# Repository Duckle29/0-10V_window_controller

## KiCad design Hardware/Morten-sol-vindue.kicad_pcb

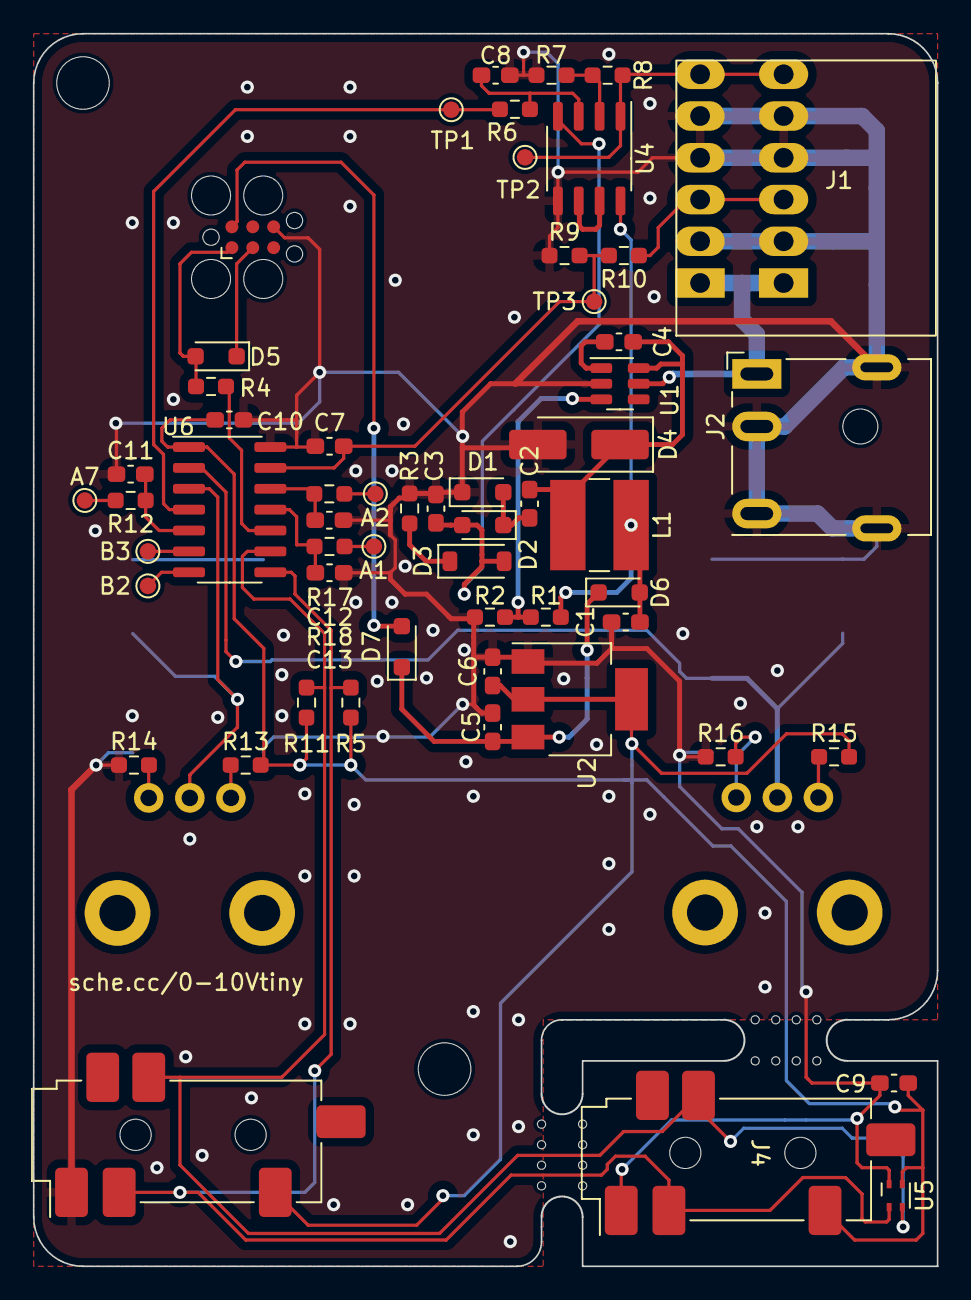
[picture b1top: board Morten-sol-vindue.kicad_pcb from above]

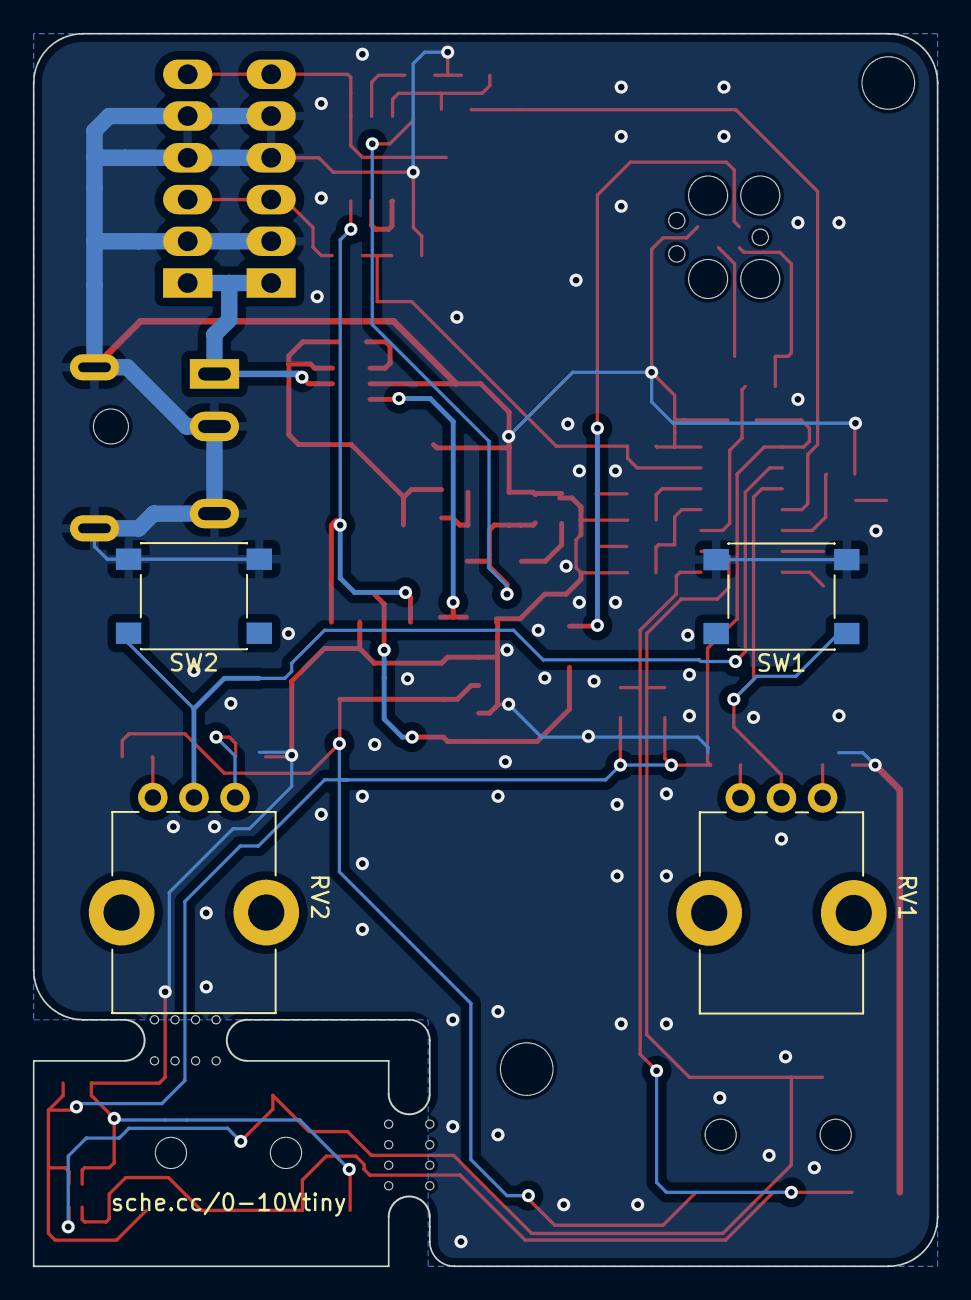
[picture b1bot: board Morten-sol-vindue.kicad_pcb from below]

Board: 2 copper layers, 55.0 x 75.0 mm, 61 parts (4 on the bottom side), 38 nets.

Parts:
A1, A2, A7: PA7; TestPoint_Pad_D1.0mm
B2, B3: PA7; TestPoint_Pad_D1.0mm
C1, C2, C3, C5, C6: 1uF 25V; C_0603_1608Metric_Pad1.08x0.95mm_HandSolder
C4, C7, C8, C9, C10, C11, C12, C13: 100nF; C_0603_1608Metric_Pad1.08x0.95mm_HandSolder
D1, D2, D5, D6, D7: BAT54WS; D_SOD-323_HandSoldering
D3: 15V; D_SOD-123
D4: SS12; D_SMA_Handsoldering
J1: CUI TBL009-254-06xx; TerminalBlock_Phoenix_PTSM-0,5-6-2.5-H-THR_1x06_P2.50mm_Hor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
J2: CUI_PJ-079BH; BarrelJack_CUI_PJ-079BH_Horizontal
J3: SJ-43514-SMT; Jack_3.5mm_CUI_SJ-43516-SMT_Horizontal
J4: AudioJack4; Jack_3.5mm_CUI_SJ-43516-SMT_Horizontal
J5: AVR-UPDI-6; Tag-Connect_TC2030-IDC-FP_2x03_P1.27mm_Vertical
L1: 1mH; L_TracoPower_TCK-047_5.2x5.8mm
R1: 150k; R_0603_1608Metric_Pad0.98x0.95mm_HandSolder
R2: 10k; R_0603_1608Metric_Pad0.98x0.95mm_HandSolder
R3, R12, R17, R18: 100R; R_0603_1608Metric_Pad0.98x0.95mm_HandSolder
R4: 470R; R_0603_1608Metric_Pad0.98x0.95mm_HandSolder
R5, R10, R11: 12k; R_0603_1608Metric_Pad0.98x0.95mm_HandSolder
R6, R14, R16: 1k; R_0603_1608Metric_Pad0.98x0.95mm_HandSolder
R7, R13, R15: 33k; R_0603_1608Metric_Pad0.98x0.95mm_HandSolder
R8: 100k; R_0603_1608Metric_Pad0.98x0.95mm_HandSolder
R9: 3k9; R_0603_1608Metric_Pad0.98x0.95mm_HandSolder
RV1, RV2: 100K; Potentiometer_Bourns_PTV09A-1_Single_Vertical
SW1, SW2: SW_Push; SW_Push_1P1T_NO_6x6mm_H9.5mm
TP1: DAC; TestPoint_Pad_D1.0mm
TP2: DACx4; TestPoint_Pad_D1.0mm
TP3: A3(0-10/~4); TestPoint_Pad_D1.0mm
U1: LV2862YDDCR; SOT-23-6
U2: AMS1117-3.3; SOT-223-3_TabPin2
U4: LM358; SO-8_3.9x4.9mm_P1.27mm
U5: SHT4x; Sensirion_DFN-4_1.5x1.5mm_P0.8mm_SHT4x_NoCentralPad
U6: ATtiny414-SS; SOIC-14_3.9x8.7mm_P1.27mm

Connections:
+3V3: C6.2, C9.2, C10.2, J3.T, J4.T, R5.1, R11.1, R13.2, R15.2, U2.2 (VO), U5.3 (VDD), U6.1 (VCC)
+12VA: C1.1, D6.2 (A), L1.2, R1.1, U4.8 (V+)
+24V: J1.1, J2.1, U1.5 (VIN)
-12VA: C3.2, D2.2 (A), D3.2 (A), U4.4 (V-)
/0-10V in: J1.3, R10.1
/0-10V out: J1.6, R8.2, TP2.1, U4.1
/Adapter RX: D5.2 (A), J5.1 (DATA), R4.2
/UPDI: R4.1, U6.10 (~RESET/PA0)
GND: C1.2, C3.1, C5.1, C6.1, C7.1, C8.1, C9.1, C10.1, C11.1, C12.1, C13.1, D1.1 (K), D4.2 (A), J1.2, J1.4, J1.5, J2.2, J2.3, J2.MP (MountPin), J3.S, J4.S, J5.6 (GND), R2.2, R3.2, R7.2, R9.1, R14.1, R16.1, SW1.2, SW2.2, U1.2 (GND), U2.1 (GND), U4.5 (+), U5.4 (VSS), U6.14 (GND)
unnamed: A1.1, R18.2
unnamed: A2.1, R17.2
unnamed: A7.1, R12.2
unnamed: C2.2, D1.2 (A), D2.1 (K)
unnamed: D3.1 (K), R3.1
unnamed: C2.1, C4.2, D4.1 (K), L1.1, U1.6 (SW)
unnamed: D5.1 (K), J5.3 (TX)
unnamed: C5.2, D6.1 (K), D7.1 (K), U2.3 (VI)
unnamed: R13.1, RV1.1
unnamed: R14.2, RV1.3
unnamed: R15.1, RV2.1
unnamed: R16.2, RV2.3
unnamed: C4.1, U1.1 (CB)
unnamed: R1.2, R2.1, U1.3 (FB)
unnamed: C8.2, R6.2, U4.3 (+)
unnamed: R7.1, R8.1, U4.2 (-)
unnamed: U4.6 (-), U4.7
unnamed: C13.2, R18.1, U6.11 (PA1)
unnamed: C12.2, R17.1, U6.12 (PA2)
unnamed: C7.2, R9.2, R10.2, TP3.1, U6.13 (PA3)
unnamed: R6.1, TP1.1, U6.4 (PA6)
unnamed: C11.2, R12.1, U6.5 (PA7)
unnamed: B2.1, U6.7 (PB2)
unnamed: B3.1, U6.6 (PB3)
SCL: J3.R1, J4.R1, R11.2, U5.2 (SCL), U6.9 (PB0)
SDA: J3.R2, J4.R2, R5.2, U5.1 (SDA), U6.8 (PB1)
VBUS: D7.2 (A), J5.2 (VCC)
closed_SP: RV1.2, SW1.1, U6.3 (PA5)
open_SP: RV2.2, SW2.1, U6.2 (PA4)

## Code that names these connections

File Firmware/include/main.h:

#include <Arduino.h>
#include <Wire.h>
#include <avr/sleep.h>

#include "sht4x.h"

#define NO_SERIAL

const uint8_t pin_feedback = PIN_PA3;
const uint8_t pin_dac = PIN_PA6;
const uint8_t pin_open = PIN_PA4;
const uint8_t pin_close = PIN_PA5;

const uint8_t unused_pins[] = {
    //PIN_PB2, PIN_PB3, // UART
    PIN_PA1, PIN_PA2, PIN_PA7
};

const uint16_t dial_range[] = {10, 985};
const uint16_t closed_range[] = {2000, 5000}; // 20-50C
const uint16_t open_range[] = {1000, 4000}; // 10-40C
const uint16_t max_temp = 12500; // 0-125C. uint will overflow to >600C
const uint8_t pos_out_range[] = {20, 235}; // 0.784 - 9.22V. Actuator closed-open range is 1-9V

// Actuator should be able to move a full 400mm stroke in ~90s
const uint16_t pos_timeout = 10; // [s]
const uint16_t pos_deadband_mm = 10; // [mm]
const uint16_t stroke = 400; // [mm]

const uint8_t pos_deadband_ticks = pos_deadband_mm * 255 / stroke; // [DAC ticks]
 
// As the mcu sleeps most of the time, we can't rely on millis()
uint16_t ticks = 0;
const uint16_t tick_rate = 2;
const uint16_t pos_timeout_ticks = pos_timeout * tick_rate;

uint16_t sp_closed, sp_open;
uint8_t old_pos, new_pos = 0;
uint16_t deadline = 0 + 2*pos_timeout_ticks;

bool force_close, force_open = false;

uint8_t get_pos_out(uint16_t temp, uint16_t sp_closed, uint16_t sp_open);
void prepare_sleep();
void go_sleep();
void RTC_init();

SHT4x sht40;

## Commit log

2023-04-30 Create LICENSE
2023-05-08 Initial layout
2023-05-09 Re-layout
2023-05-09 Added PCB renders
2023-06-06 hmmm
2023-06-18 Full functionality
2023-06-18 Tweak pot ranges
